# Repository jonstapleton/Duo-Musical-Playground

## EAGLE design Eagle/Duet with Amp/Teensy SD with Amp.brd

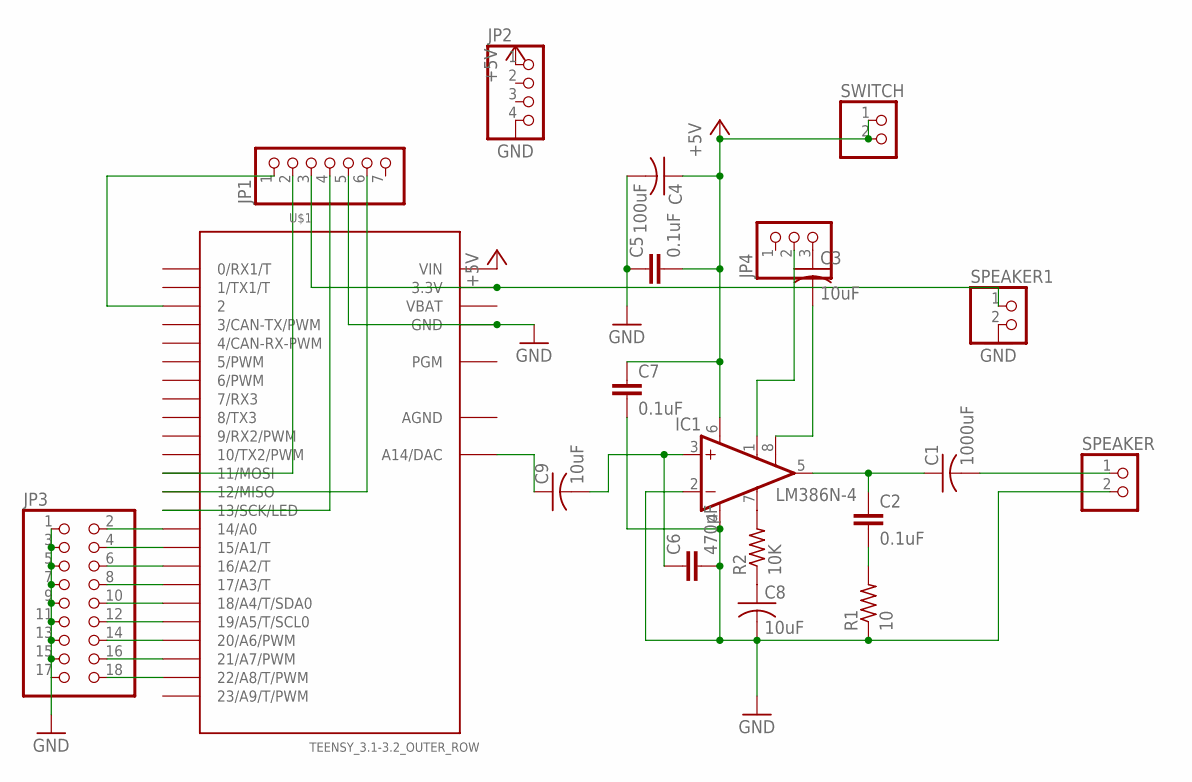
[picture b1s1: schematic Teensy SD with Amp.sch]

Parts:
C1: 1000uF; C025-030X050
C2, C5, C7: 0.1uF; C2.5-4
C3, C8, C9: 10uF; C025-030X050
C4: 100uF; C025-030X050
C6: 470pF; C2.5-4
IC1: LM386N-4; DIL08
JP1: PINHD-1X7; 1X07
JP2: PINHD-1X4; 1X04
JP3: PINHD-2X9; 2X09
JP4: PINHD-1X3; 1X03
R1: 10; 0207/7
R2: 10K; 0207/7
SPEAKER, SPEAKER1: PINHD-1X2; 1X02
SWITCH: PINHD-1X2; 1X02
U$1: TEENSY_3.1-3.2_OUTER_ROW; TEENSY_3.0-3.2&LC_OUTER_ROW

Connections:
+5V: C4.1, C5.2, C7.1, IC1.6 (VS), JP2.1, SWITCH.1, SWITCH.2, U$1.VIN
AGND: U$1.AGND
GND: C4.2, C5.1, C6.2, C7.2, C8.2, IC1.2 (-IN), IC1.4 (GND), JP1.5, JP2.4, JP3.1, JP3.3, JP3.5, JP3.7, JP3.9, JP3.11, JP3.13, JP3.15, JP3.17, R1.1, SPEAKER.2, SPEAKER1.2, U$1.GND, U$1.GND1 (GND)
unnamed: C3.1, JP4.3
unnamed: C3.2, IC1.8 (GAIN)
unnamed: C1.1, C2.1, IC1.5 (OUT)
unnamed: IC1.7 (BYPASS), R2.2
unnamed: C8.1, R2.1
unnamed: C6.1, C9.2, IC1.3 (+IN)
unnamed: C2.2, R1.2
unnamed: JP1.3, SPEAKER1.1, U$1.3.3V, U$1.3.3V1 (3.3V)
unnamed: C1.2, SPEAKER.1
unnamed: JP3.18, U$1.22/A8 (22/A8/T/PWM)
unnamed: JP1.4, U$1.13 (13/SCK/LED)
unnamed: JP1.2, U$1.11 (11/MOSI)
unnamed: JP1.6, U$1.12 (12/MISO)
unnamed: JP3.16, U$1.21/A7 (21/A7/PWM)
unnamed: JP3.14, U$1.20/A6 (20/A6/PWM)
unnamed: JP3.12, U$1.19/A5 (19/A5/T/SCL0)
unnamed: JP3.10, U$1.18/A4 (18/A4/T/SDA0)
unnamed: JP3.8, U$1.17/A3 (17/A3/T)
unnamed: JP3.6, U$1.16/A2 (16/A2/T)
unnamed: JP3.4, U$1.15/A1 (15/A1/T)
unnamed: JP3.2, U$1.14/A0
unnamed: C9.1, U$1.RESET/DAC (A14/DAC)
unnamed: IC1.1 (GAIN), JP4.2
unnamed: JP1.1, U$1.2
VBAT: U$1.VBAT

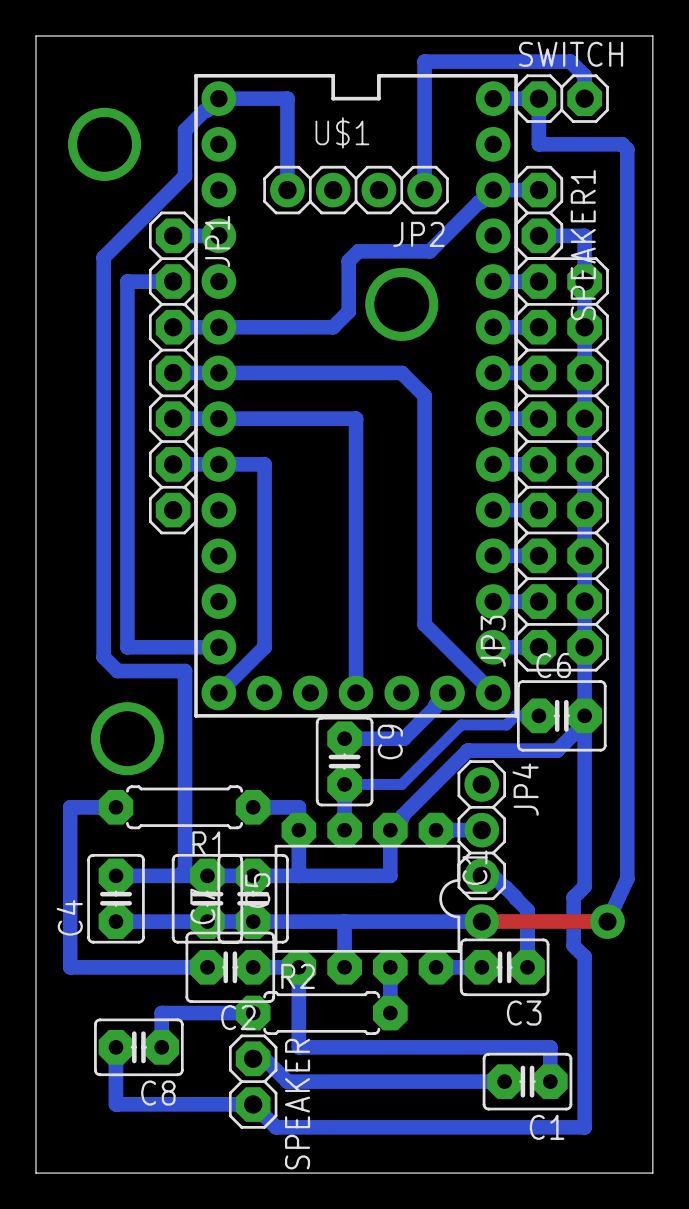
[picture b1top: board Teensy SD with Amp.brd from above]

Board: 2 copper layers, 34.3 x 63.2 mm, 20 parts (0 on the bottom side), 26 nets.

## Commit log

2017-08-16 Initial sketch upload
    Includes all sampler iterations to date, along with .h and .cpp files
2017-08-22 Jellyfish updates
    Changed pins to those needed for the jellyfish. Also includes Julian’s
    update to the code.
2017-09-24 Initial upload
2017-09-24 Traced to 32mils
2017-10-06 Revert "Traced to 32mils"
    This reverts commit ffbe95997752b5ed6823b856a1fed8613c21e4f0.
2017-10-06 Fixed tracing to 16mils
2017-12-09 Adding a folder for my Duo Projects
2017-12-09 Adding all my Duo files to this folder
2017-12-11 Template for NFC Code
    Julian added script so we can identify the uid as cardA, cardB, etc.
2017-12-11 Organizing
    Created Folders for various projects to keep them straight.
2017-12-13 ArduinoNFCTeensyPinAssignments
2017-12-13 NFC Teensy Pins
2017-12-15 Audio NFC Test
2017-12-15 Changed SPI pin assignments
2017-12-15 Not include Wire library
2017-12-15 Audio memory allocated
2017-12-15 Pin assignments 2.0
2017-12-17 Updates
    Eric’s code from Dec project class. NFC stuff.
2018-01-02 Blanket Files
    I adapted the Nama Fritz file to reflect the schematics I will use.
    This minimizes wire overlap and accounts for the layout of the new
    LilyPad power chip that I’m using. I have not changed the pins in the
    Arduino file yet.
2018-01-04 New Xmas Tree Wall hanging file
    This one doesn’t play Jingle Bells.
2018-01-10 Skidamarink song
2018-01-28 Darya Melody
2018-02-10 Duo Project Camp files
2018-08-16 Blanket project updates
    Finished Arduino Sketch and added ASCII converter to the max patch
2018-09-20 Updates to Duo Code
    Working on new code for October Level-Up classes
2018-09-23 Magic Wand Work
2019-02-05 Mu CircuitPython files
    Started using My and CircuitPython to code Circuit Playgrounds
